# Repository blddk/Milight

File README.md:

# Milight
Board to replace the controller inside Milight 6W E27 bulbs

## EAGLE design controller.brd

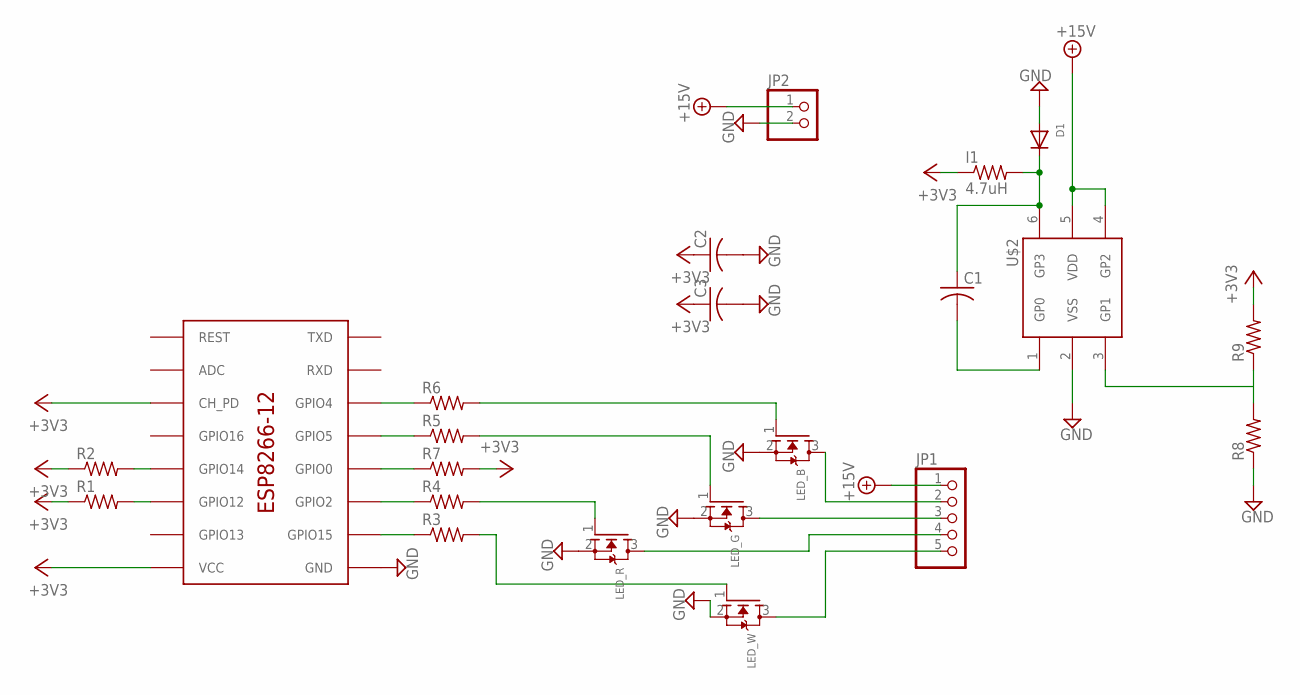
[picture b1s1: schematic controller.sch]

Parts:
C1, C2, C3: C-USC0805; C0805
D1: DIODESOT23_REFLOW; SOT23-R
I1: 4.7uH; R0805
JP1: PINHD-1X5; 1X05
JP2: PINHD-1X2; 1X02
LED_B: MOSFET-NREFLOW; SOT23
LED_G: MOSFET-NREFLOW; SOT23
LED_R: MOSFET-NREFLOW; SOT23
LED_W: MOSFET-NREFLOW; SOT23
R1, R2, R3, R4, R5, R6, R7, R8, R9: R-US_R0805; R0805
U$1: ESP8266-12
U$2: 10F200T; SOT23-6

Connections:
+3V3: C2.1, C3.1, I1.1, R1.1, R2.1, R7.2, R9.2, U$1.CH_PD, U$1.VCC
+15V: JP1.1, JP2.1, U$2.4 (GP2), U$2.5 (VDD)
GND: C2.2, C3.2, D1.1 (A), JP2.2, LED_B.2 (S), LED_G.2 (S), LED_R.2 (S), LED_W.2 (S), R8.1, U$1.GND, U$2.2 (VSS)
GPIO0: R7.1, U$1.GPIO0
GPIO2: R4.1, U$1.GPIO2
GPIO4: R6.1, U$1.GPIO4
GPIO5: R5.1, U$1.GPIO5
GPIO12: R1.2, U$1.GPIO12
GPIO14: R2.2, U$1.GPIO14
GPIO15: R3.1, U$1.GPIO15
unnamed: JP1.5, LED_W.3 (D)
unnamed: JP1.4, LED_R.3 (D)
unnamed: JP1.2, LED_B.3 (D)
unnamed: JP1.3, LED_G.3 (D)
unnamed: C1.1, D1.3 (C), I1.2, U$2.6 (GP3)
unnamed: C1.2, U$2.1 (GP0)
unnamed: LED_W.1 (G), R3.2
unnamed: LED_R.1 (G), R4.2
unnamed: LED_G.1 (G), R5.2
unnamed: LED_B.1 (G), R6.2
unnamed: R8.2, R9.1, U$2.3 (GP1)

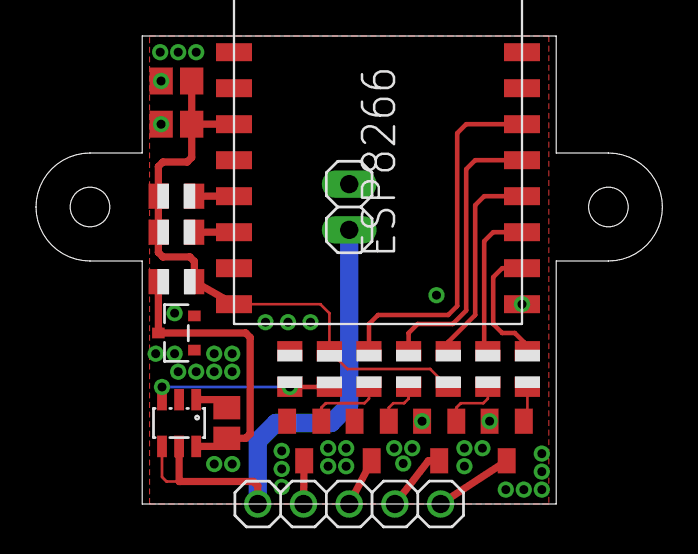
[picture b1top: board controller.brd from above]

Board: 2 copper layers, 34.8 x 26.0 mm, 23 parts (1 on the bottom side), 21 nets.

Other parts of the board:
U$3: CAPTAIN_SLOW_SMALL
